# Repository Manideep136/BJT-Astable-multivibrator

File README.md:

# BJT-Astable-multivibrator

## 📌 Project Overview

The **BJT Astable Multivibrator** is a transistor-based oscillator circuit that continuously switches between two states without using an IC.

The circuit is built using two **2N3904 NPN transistors**, two LEDs, resistors, and capacitors. The two transistor stages are cross-coupled through capacitors, causing the transistors to turn ON and OFF alternately.

As a result, the two LEDs blink alternately, demonstrating the basic principles of **transistor switching, capacitor charging/discharging, feedback, and oscillation**.

The complete circuit and PCB were designed using **KiCad 9.0**.

---

## 🎯 Objectives

The main objectives of this project are:

- Understand the working principle of an astable multivibrator.
- Learn transistor switching using NPN transistors.
- Understand capacitor charging and discharging.
- Study cross-coupled transistor circuits.
- Design a complete schematic using KiCad.
- Assign appropriate footprints to components.
- Design and route a PCB.
- Perform ERC and DRC checks.
- Understand the relationship between resistor/capacitor values and oscillation frequency.

---

## ⚙️ Circuit Overview

The circuit consists of two **2N3904 NPN transistors** connected in a cross-coupled configuration.

Each transistor has:

- A collector resistor
- A base resistor
- An LED in the collector branch
- A coupling capacitor connected to the opposite transistor

The circuit is powered by a **3.7 V DC supply**.

### Basic Circuit Structure

```text
              +3.7V
                │
          ┌─────┴─────┐
          │           │
         R1          R4
        1 kΩ        1 kΩ
          │           │
         LED1        LED2
          │           │
         Q1          Q2
      2N3904      2N3904
          │           │
         GND         GND

       Cross-Coupled
       Capacitor Network

        Q1 Collector
             │
             C1
             │
        Q2 Base

        Q2 Collector
             │
             C2
             │
        Q1 Base

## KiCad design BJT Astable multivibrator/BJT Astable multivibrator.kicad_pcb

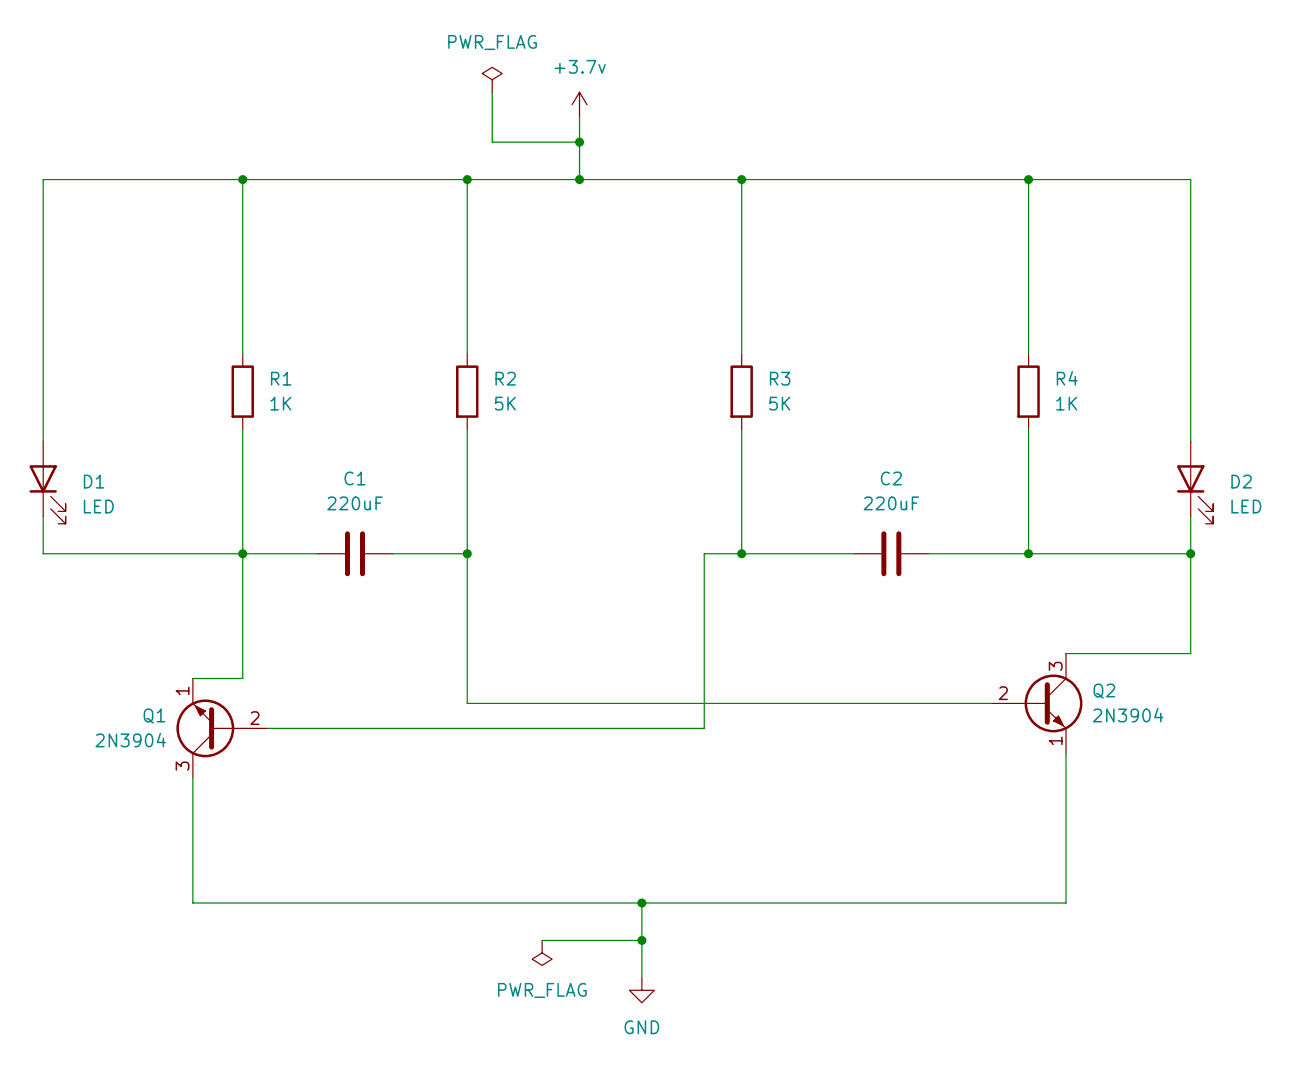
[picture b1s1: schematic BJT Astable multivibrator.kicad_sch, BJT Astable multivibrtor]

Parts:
C1, C2: 220uF; CP_Radial_D5.0mm_P2.50mm
D1, D2: LED; LED_D3.0mm
Q1, Q2: 2N3904; TO-92_Inline
R1, R4: 1K; R_Axial_DIN0204_L3.6mm_D1.6mm_P2.54mm_Vertical
R2, R3: 5K; R_Axial_DIN0204_L3.6mm_D1.6mm_P2.54mm_Vertical

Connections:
+3.7v: D1.2 (A), D2.2 (A), R1.1, R2.1, R3.1, R4.1
GND: Q1.3 (C), Q2.1 (E)
unnamed: C1.1, D1.1 (K), Q1.1 (E), R1.2
unnamed: C2.2, D2.1 (K), Q2.3 (C), R4.2
unnamed: C2.1, Q1.2 (B), R3.2
unnamed: C1.2, Q2.2 (B), R2.2

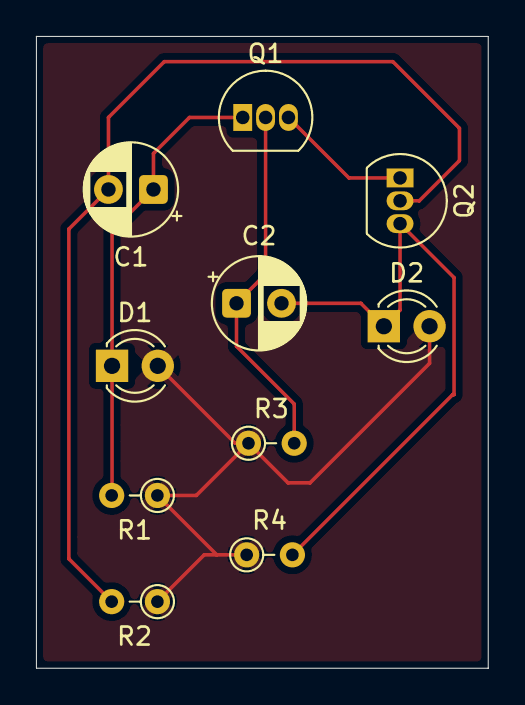
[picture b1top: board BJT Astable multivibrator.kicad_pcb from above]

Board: 2 copper layers, 25.1 x 35.1 mm, 10 parts (0 on the bottom side), 6 nets.
